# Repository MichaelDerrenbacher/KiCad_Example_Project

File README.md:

# KiCad_Example_Project
Inverting op-amp with gain of 10 schematic and layout

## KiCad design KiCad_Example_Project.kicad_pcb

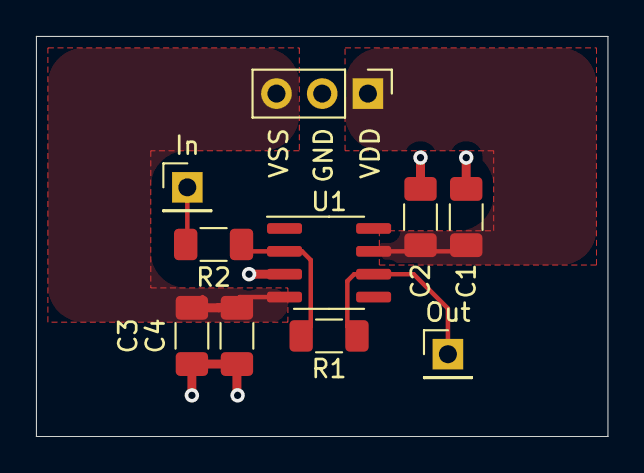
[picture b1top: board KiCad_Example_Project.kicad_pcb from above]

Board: 2 copper layers, 31.8 x 22.2 mm, 10 parts (0 on the bottom side), 6 nets.

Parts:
C1, C3: 1u; C_1206_3216Metric_Pad1.33x1.80mm_HandSolder
C2, C4: 100n; C_1206_3216Metric_Pad1.33x1.80mm_HandSolder
GND: Conn_01x03_Male; PinHeader_1x03_P2.54mm_Vertical
In: Conn_01x01_Male; PinHeader_1x01_P2.54mm_Vertical
Out: Conn_01x01_Male; PinHeader_1x01_P2.54mm_Vertical
R1: 100k; R_1206_3216Metric_Pad1.30x1.75mm_HandSolder
R2: 10k; R_1206_3216Metric_Pad1.30x1.75mm_HandSolder
U1: OP07; SOIC-8_3.9x4.9mm_P1.27mm

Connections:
0: C1.2, C2.2, C3.1, C4.1, GND.2, U1.3
In: In.1, R2.2
unnamed: R1.2, R2.1, U1.2
Out: Out.1, R1.1, U1.6
VDD: C1.1, C2.1, GND.1, U1.7
VSS: C3.2, C4.2, GND.3, U1.4

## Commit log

2021-03-11 Kicad project files upload
2021-03-11 Output Gerber Files
